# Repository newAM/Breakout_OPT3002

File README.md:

## OPT3002 I2C Ambient Light Sensor Breakout

This project is a PCB breakout for the Texas Instruments OPT3002 I2C ambient light sensor.

## Media

## Project Contents
-  Breakout_OPT3002_KiCAD - KiCad PCB and schematic files
-  Breakout_OPT3002_Media - photos

## Software Used
- [KiCad](http://kicad-pcb.org/) 5.0.0 release

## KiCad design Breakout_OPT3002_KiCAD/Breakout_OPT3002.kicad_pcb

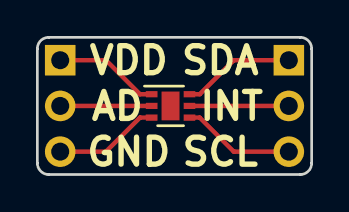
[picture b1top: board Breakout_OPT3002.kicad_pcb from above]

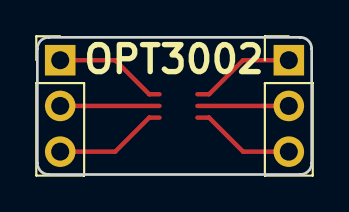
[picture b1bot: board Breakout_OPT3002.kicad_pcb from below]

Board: 2 copper layers, 15.2 x 7.6 mm, 3 parts (2 on the bottom side), 6 nets.

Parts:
U1: OPT3002; DFN-6-1EP_2x2mm_Pitch0.65mm
X1, X2: Conn_01x03; Pin_Header_Straight_1x03_Pitch2.54mm

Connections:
unnamed: U1.1, X1.1
unnamed: U1.2, X1.2
unnamed: U1.3, X1.3
unnamed: U1.4, X2.3
unnamed: U1.5, X2.2
unnamed: U1.6, X2.1

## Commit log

2018-09-09 cropped rendering
2018-10-09 corrected typo in README
2021-11-09 Update kicad URL
    https://forum.kicad.info/t/warning-avoid-all-links-to-kicad-pcb-org-use-kicad-org/31521
